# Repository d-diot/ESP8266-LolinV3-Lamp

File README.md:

# ESP8266-LolinV3-Lamp

This board is part of the [d-diot project](https://www.d-diot.com) and it is part of the [d-diot mood lamp](https://github.com/d-diot/mood-lamp).
Visit the [dedicated wiki page](https://wiki.d-diot.com/hardware/pcb/esp/esp8266-lolinv3-lamp) to know more.

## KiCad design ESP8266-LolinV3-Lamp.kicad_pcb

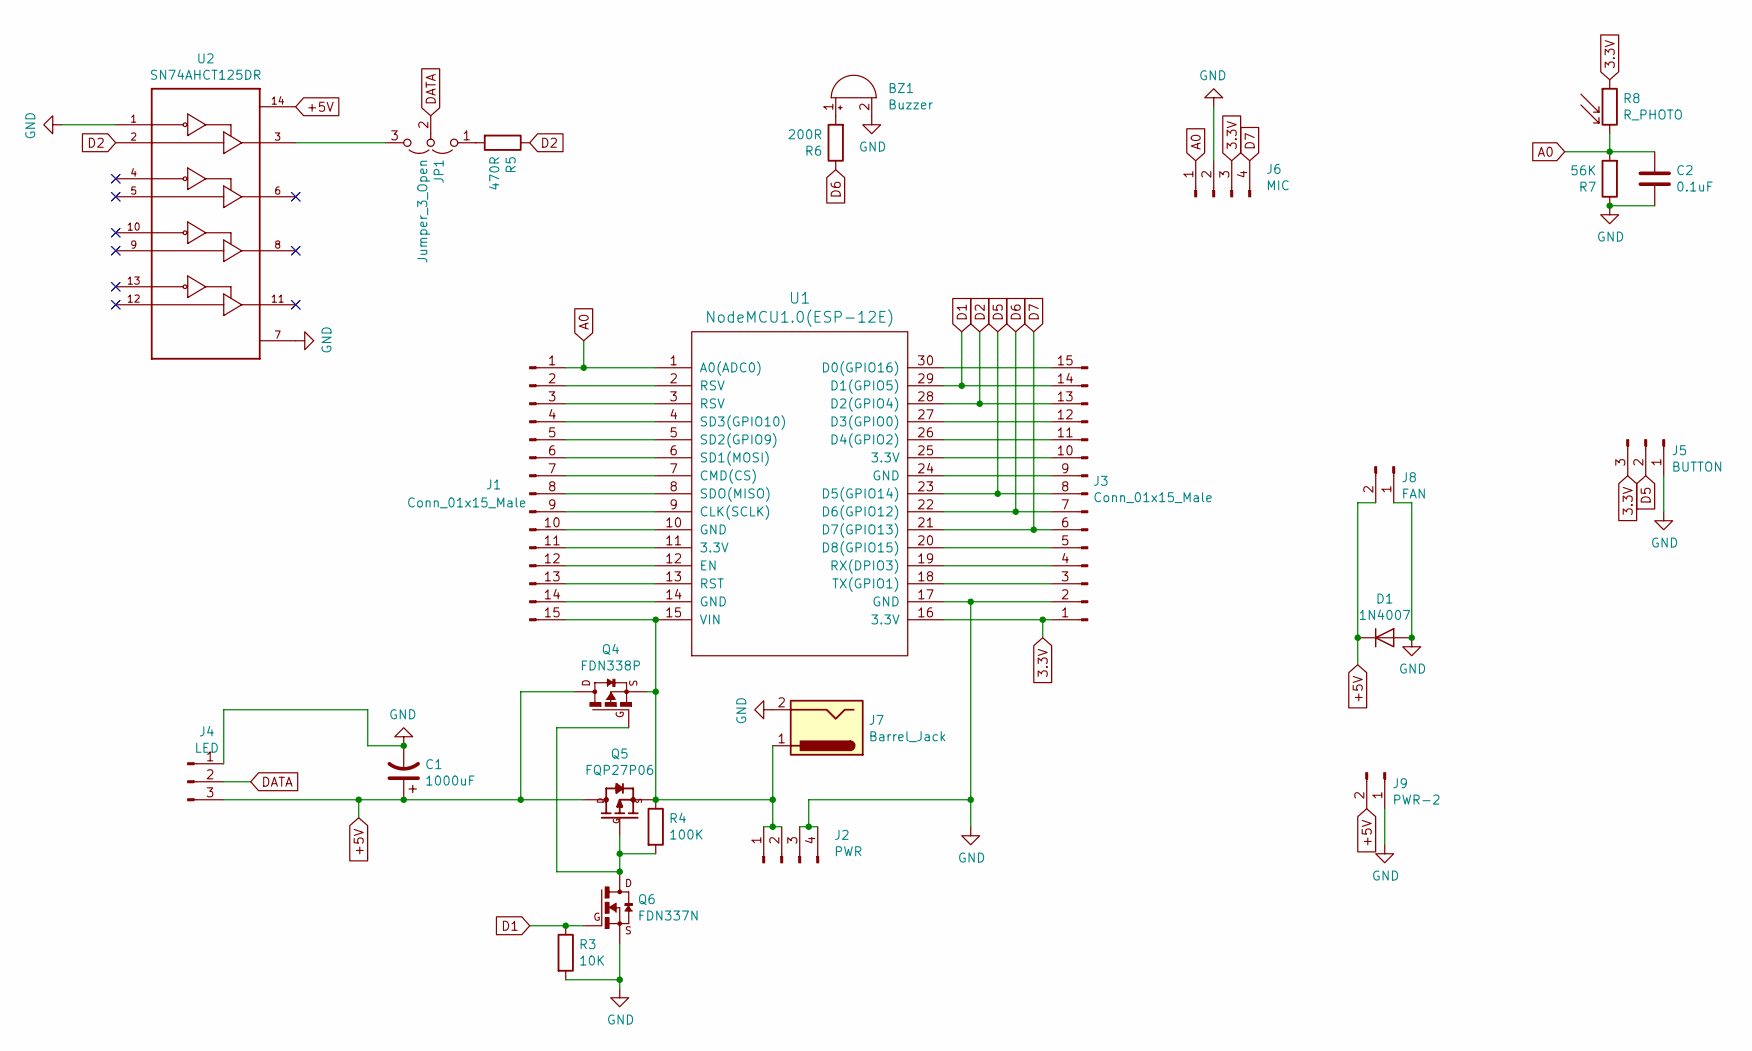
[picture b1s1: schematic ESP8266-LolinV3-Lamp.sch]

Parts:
BZ1: Buzzer; Buzzer_12x9.5RM7.6
C1: 1000uF; CP_Radial_D10.0mm_P5.00mm
C2: 0.1uF; C_Disc_D6.0mm_W4.4mm_P5.00mm
D1: 1N4007; D_DO-41_SOD81_P10.16mm_Horizontal
J1, J3: Conn_01x15_Male; PinHeader_1x15_P2.54mm_Vertical
J2: PWR; PinHeader_1x04_P2.54mm_Vertical
J4: LED; PinHeader_1x03_P2.54mm_Vertical
J5: BUTTON; PinHeader_1x03_P2.54mm_Vertical
J6: MIC; PinHeader_1x04_P2.54mm_Vertical
J7: Barrel_Jack; BarrelJack_Wuerth_6941xx301002
J8: FAN; PinHeader_1x02_P2.54mm_Vertical
J9: PWR-2; PinHeader_1x02_P2.54mm_Vertical
JP1: Jumper_3_Open; PinHeader_1x03_P2.54mm_Vertical
Q4: FDN338P; SSOT-3
Q5: FQP27P06; TO-220-3_Vertical
Q6: FDN337N; SSOT-3
R3: 10K; R_Axial_DIN0207_L6.3mm_D2.5mm_P7.62mm_Horizontal
R4: 100K; R_Axial_DIN0207_L6.3mm_D2.5mm_P7.62mm_Horizontal
R5: 470R; R_Axial_DIN0207_L6.3mm_D2.5mm_P7.62mm_Horizontal
R6: 200R; R_Axial_DIN0207_L6.3mm_D2.5mm_P7.62mm_Horizontal
R7: 56K; R_Axial_DIN0207_L6.3mm_D2.5mm_P7.62mm_Horizontal
R8: R_PHOTO; R_LDR_5.0x4.1mm_P3mm_Vertical
U1: NodeMCU1.0(ESP-12E); NodeMCU-LoLinV3
U2: SN74AHCT125DR; SOIC127P600X175-14N

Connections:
3.3V: J3.1, J5.3, J6.3, R8.1, U1.16 (3.3V)
+5V: C1.1, D1.1 (K), J4.3, J8.2, J9.2, Q4.3 (D), Q5.2 (D), Q5.HEAT (D), U2.14 (VCC)
A0: C2.1, J1.1, J6.1, R7.2, R8.2, U1.1 (A0(ADC0))
D1: J3.14, Q6.1 (G), R3.1, U1.29 (D1(GPIO5))
D2: J3.13, R5.1, U1.28 (D2(GPIO4)), U2.2 (1A)
D5: J3.8, J5.2, U1.23 (D5(GPIO14))
D6: J3.7, R6.1, U1.22 (D6(GPIO12))
D7: J3.6, J6.4, U1.21 (D7(GPIO13))
DATA: J4.2, JP1.2 (C)
GND: BZ1.2 (+), C1.2, C2.2, D1.2 (A), J2.3, J2.4, J3.2, J4.1, J5.1, J6.2, J7.2, J8.1, J9.1, Q6.2 (S), R3.2, R7.1, U1.17 (GND), U2.1 (1!OE), U2.7 (GND)
unnamed: BZ1.1 (-), R6.2
unnamed: J1.2, U1.2 (RSV)
unnamed: J1.3, U1.3 (RSV)
unnamed: J1.4, U1.4 (SD3(GPIO10))
unnamed: J1.5, U1.5 (SD2(GPIO9))
unnamed: J1.6, U1.6 (SD1(MOSI))
unnamed: J1.7, U1.7 (CMD(CS))
unnamed: J1.8, U1.8 (SDO(MISO))
unnamed: J1.9, U1.9 (CLK(SCLK))
unnamed: J1.10, U1.10 (GND)
unnamed: J1.11, U1.11 (3.3V)
unnamed: J1.12, U1.12 (EN)
unnamed: J1.13, U1.13 (RST)
unnamed: J1.14, U1.14 (GND)
unnamed: J1.15, J2.1, J2.2, J7.1, Q4.2 (S), Q5.3 (S), R4.1, U1.15 (VIN)
unnamed: J3.3, U1.18 (TX(GPIO1))
unnamed: J3.4, U1.19 (RX(DPIO3))
unnamed: J3.5, U1.20 (D8(GPIO15))
unnamed: J3.9, U1.24 (GND)
unnamed: J3.10, U1.25 (3.3V)
unnamed: J3.11, U1.26 (D4(GPIO2))
unnamed: J3.12, U1.27 (D3(GPIO0))
unnamed: J3.15, U1.30 (D0(GPIO16))
unnamed: JP1.1 (A), R5.2
unnamed: JP1.3 (B), U2.3 (1Y)
unnamed: Q4.1 (G), Q5.1 (G), Q6.3 (D), R4.2

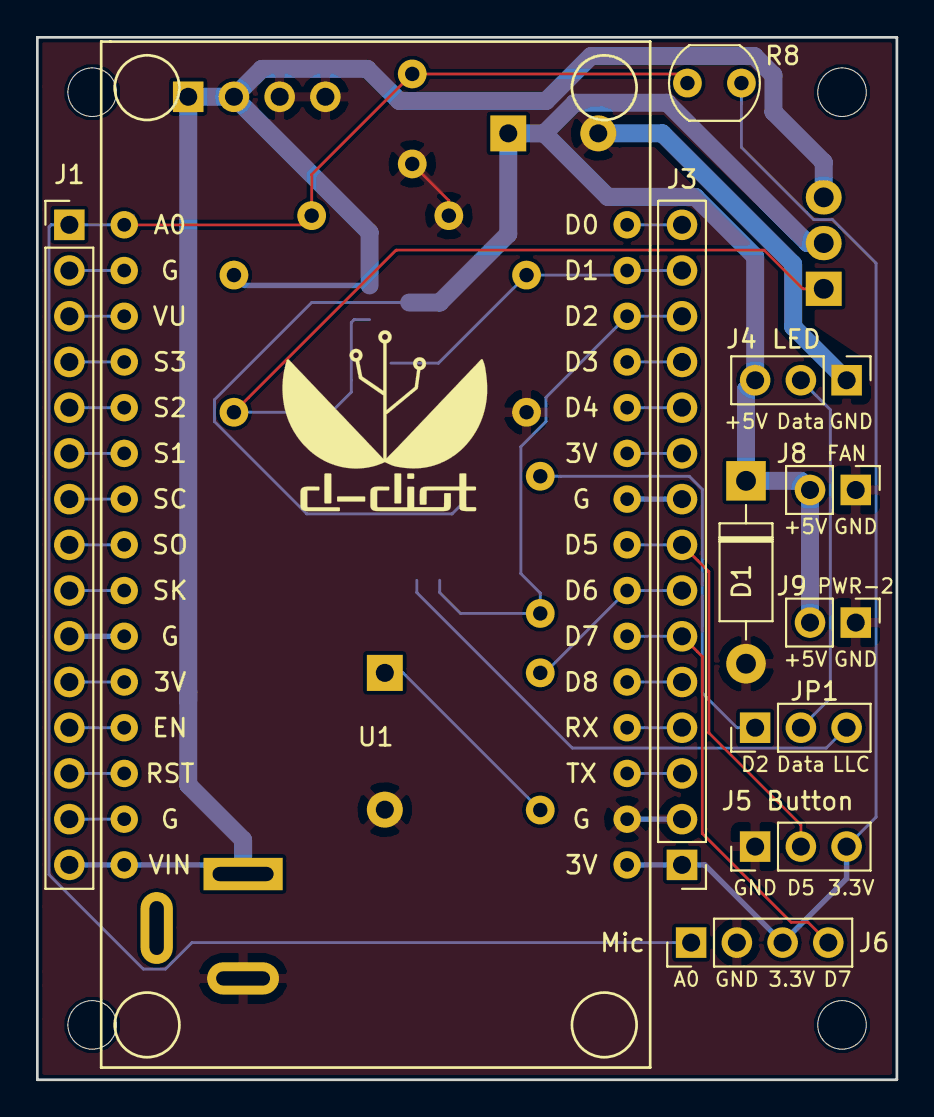
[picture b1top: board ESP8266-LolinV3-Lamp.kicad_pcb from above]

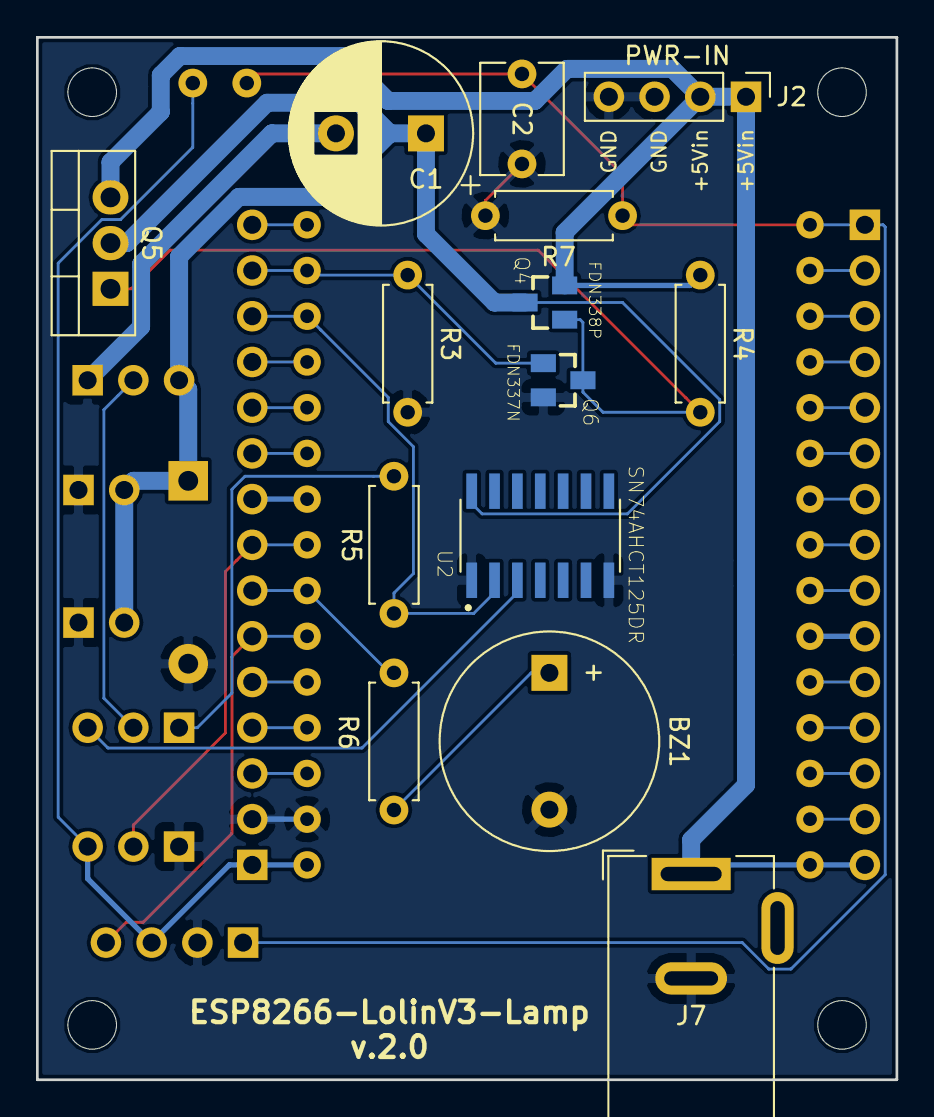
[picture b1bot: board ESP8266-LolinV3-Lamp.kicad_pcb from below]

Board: 2 copper layers, 47.8 x 57.9 mm, 25 parts (14 on the bottom side), 36 nets.

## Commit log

2019-10-11 ESP8266-LolinV3-Lamp v.1.0
2019-10-11 Added d-diot logo
2019-10-12 added photoresistor, barrel jack, 1000uF cap, LED data pin resistor
2019-12-13 Board version 2.0
2020-02-03 added Gerber files for pcbway
